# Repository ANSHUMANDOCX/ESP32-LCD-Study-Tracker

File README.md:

# ESP32-LCD-Study-Tracker
Its a Compact Server based study tracker using a OLED display and a ESP32 that help one track their study/work time on particular subjects and also lets use set a target using the interactive web page hosted on the ESP

# Parts used 
- Esp32 Wroom
- 1602 LCD Display
- PCB with onboard programmer

# Why i made this 
This device is made to solve one of the problems i face while studying i keep on getting distracted while i do something and using this device i will be able to keep track of my productive hours so i can get a reality check on long i think i am productive vs how long i actually am !!. 
# Features
- The system uses Display to set timer and keep track of your productive hours. It also has a webpage hosted on the ESP that helps you check on the hours spent at a glance. Also one can set target for the day how much time one needs to be productive for.
- It also has a Log system that logs the time we have spent on something and helps us keep track of how productive one has been. It also has a option to download the log all together as a csv file.
- There is a header for Connecting the LCD using I2C
- There are 3 Buttons for controlling the Display 'Start' , 'Stop' and , 'Change'.
- We can long press the STOP button to turnoff the backlight of the lcd since it could be distracting for some of us.

# Programming
The code is very simple you will need to import the project in platform io and once flash the system image to load the website on the ESP and next upload the main.c file thats it. Also the subject/ Topic one needs to focus on is under a placeholder so anyone can change it according to their needs.  

# PCB and Schematic and CAD

## Build 
https://youtu.be/7US3xBiMZxA?si=RdkPRtCYgrZsQL8k
https://youtu.be/MXmio46lXlo?si=qvKTUyI2eKW5zzEd

# BOM
| Serial No | Product name          | Quantity | Supplier |   Price | Total | Link                                                      |
| --------: | --------------------- | -------: | -------- | ------: | ----: | --------------------------------------------------------- |
|         1 | RC06
03JR-070RL        |      100 | LCSC     | $0.0034 | $0.34 | [LCSC](https://www.lcsc.com/product-detail/C95177.html)   |
|         2 | ME6217C33M5G          |        5 | LCSC     | $0.1219 | $0.61 | [LCSC](https://www.lcsc.com/product-detail/C427602.html)  |
|         3 | CH343P                |        1 | LCSC     | $1.1227 | $1.12 | [LCSC](https://www.lcsc.com/product-detail/C2846043.html) |
|         4 | ESP32-WROOM-32E-N4    |        1 | LCSC     | $3.7668 | $3.77 | [LCSC](https://www.lcsc.com/product-detail/C701341.html)  |
|         5 | TS-1088-AR02016       |       10 | LCSC     | $0.0531 | $0.53 | [LCSC](https://www.lcsc.com/product-detail/C720477.html)  |
|         6 | GT-TC060A-H025-L1S    |        5 | LCSC     | $0.0929 | $0.46 | [LCSC](https://www.lcsc.com/product-detail/C7450623.html) |
|         7 | FRC0603F2201TS        |      100 | LCSC     | $0.0022 | $0.22 | [LCSC](https://www.lcsc.com/product-detail/C2907005.html) |
|         8 | FRC0603F5101TS        |      100 | LCSC     | $0.0021 | $0.21 | [LCSC](https://www.lcsc.com/product-detail/C2907044.html) |
|         9 | RC0603FR-0710KL       |      100 | LCSC     | $0.0040 | $0.40 | [LCSC](https://www.lcsc.com/product-detail/C98220.html)   |
|        10 | CL10B104KB8NNNC       |      200 | LCSC     | $0.0118 | $2.36 | [LCSC](https://www.lcsc.com/product-detail/C1591.html)    |
|        11 | FRC0603F1001TS        |      100 | LCSC     | $0.0029 | $0.29 | [LCSC](https://www.lcsc.com/product-detail/C2907002.html) |
|        12 | SS8050                |       50 | LCSC     | $0.0100 | $0.50 | [LCSC](https://www.lcsc.com/product-detail/C916392.html)  |
|        13 | TYPE-C 16PIN 2MD(073) |       20 | LCSC     | $0.0707 | $1.41 | [LCSC](https://www.lcsc.com/product-detail/C2765186.html) |
|        14 | GRM188R60J476ME15D    |        5 | LCSC     | $0.1934 | $0.97 | [LCSC](https://www.lcsc.com/product-detail/C140782.html)  |
|        15 | CL10A475KP8NNNC       |       50 | LCSC     | $0.0199 | $1.00 | [LCSC](https://www.lcsc.com/product-detail/C1705.html)    |
|        16 | CL10B105KA8NNNC       |       10 | LCSC     | $0.0216 | $0.22 | [LCSC](https://www.lcsc.com/product-detail/C29936.html)   |
|        17 | CL10A106KP8NNNC       |       20 | LCSC     | $0.0353 | $0.71 | [LCSC](https://www.lcsc.com/product-detail/C19702.html)   |
|        18 | PCB       |       1 | JLC     | $2 | $2 | [JLC](jlcpcb.com)   |
|19|LCD Display|1|Robu|$2|$2|[Robu](https://robu.in/product/lcd1602-parallel-lcd-display-with-iic-i2c-interface/)|
||**TOTAL**||||20|||

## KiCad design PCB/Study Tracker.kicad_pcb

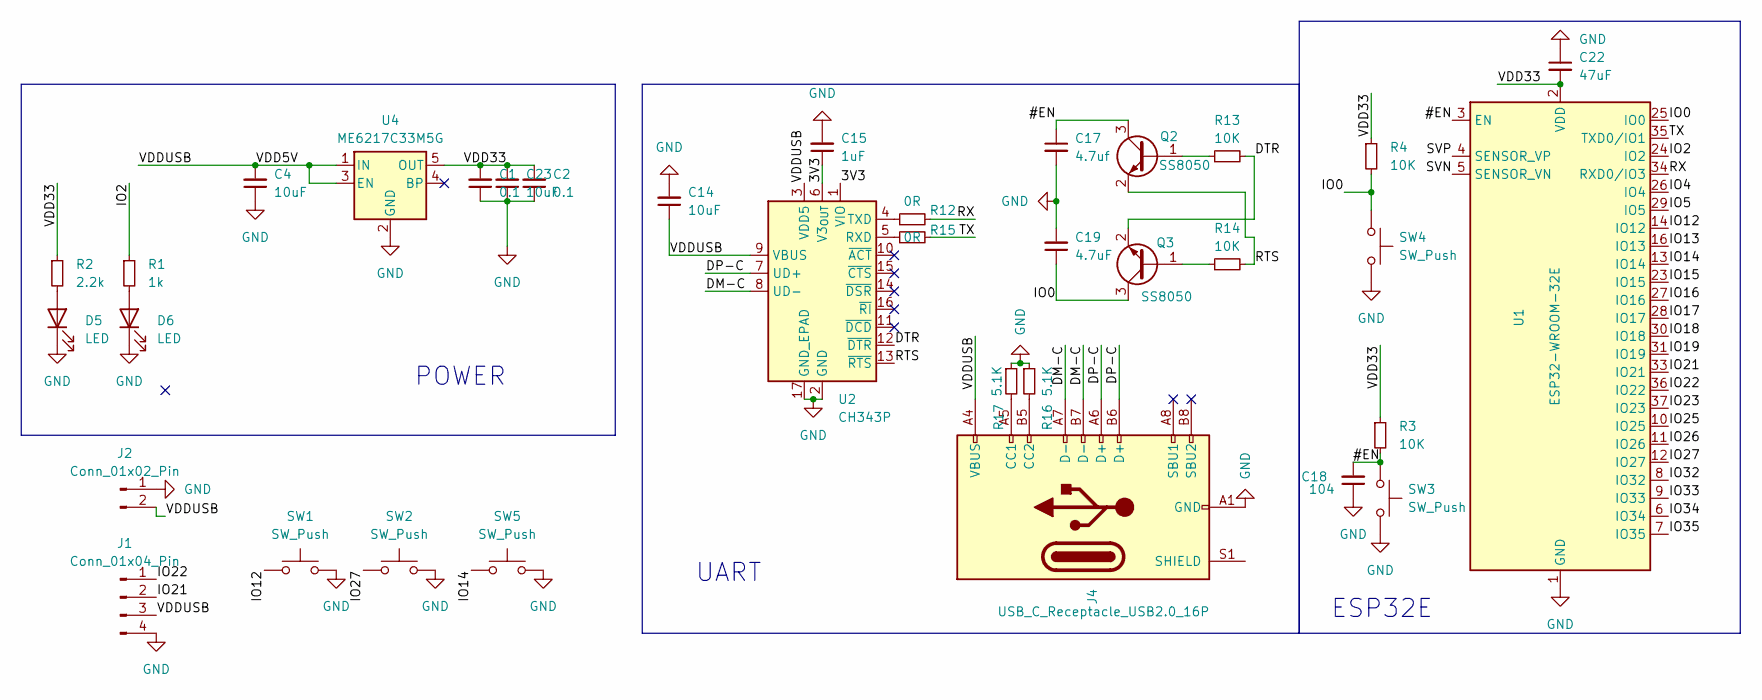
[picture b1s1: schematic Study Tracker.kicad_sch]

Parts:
C1, C2: 0.1; C_0603_1608Metric_Pad1.08x0.95mm_HandSolder
C4, C14, C23: 10uF; C_0603_1608Metric_Pad1.08x0.95mm_HandSolder
C15: 1uF; C_0603_1608Metric_Pad1.08x0.95mm_HandSolder
C17: 4.7uf; C_0603_1608Metric_Pad1.08x0.95mm_HandSolder
C18: 104; C_0603_1608Metric_Pad1.08x0.95mm_HandSolder
C19: 4.7uF; C_0603_1608Metric_Pad1.08x0.95mm_HandSolder
C22: 47uF; C_0603_1608Metric_Pad1.08x0.95mm_HandSolder
D5, D6: LED; LED_0805_2012Metric_Pad1.15x1.40mm_HandSolder
J1: Conn_01x04_Pin; PinHeader_1x04_P2.54mm_Vertical
J2: Conn_01x02_Pin; PinHeader_1x02_P2.54mm_Vertical
J4: USB_C_Receptacle_USB2.0_16P; USB_C_Receptacle_XKB_U262-16XN-4BVC11
Q2, Q3: SS8050; SOT-23
R1: 1k; R_0603_1608Metric_Pad0.98x0.95mm_HandSolder
R2: 2.2k; R_0603_1608Metric_Pad0.98x0.95mm_HandSolder
R3, R4, R13, R14: 10K; R_0603_1608Metric_Pad0.98x0.95mm_HandSolder
R12, R15: 0R; R_0603_1608Metric_Pad0.98x0.95mm_HandSolder
R16, R17: 5.1K; R_0603_1608Metric_Pad0.98x0.95mm_HandSolder
SW1, SW2, SW5: SW_Push; SW_SPST_CK_RS282G05A3
SW3, SW4: SW_Push; SW_Push_SPST_NO_Alps_SKRK
U1: ESP32-WROOM-32E; ESP32-WROOM-32D
U2: CH343P; WCH_QFN-16-1EP_3x3mm_P0.5mm_EP1.8x1.8mm
U4: ME6217C33M5G; SOT-23-5

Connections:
/3V3: C15.1, U2.1 (VIO), U2.6 (V3_{OUT})
/#EN: C17.1, C18.2, Q2.3 (C), R3.2, SW3.1, U1.3 (EN)
/DM-C: J4.A7 (D-), J4.B7 (D-), U2.8 (UD-)
/DP-C: J4.A6 (D+), J4.B6 (D+), U2.7 (UD+)
/DTR: Q3.2 (E), R13.2, U2.12 (~DTR)
/IO0: C19.1, Q3.3 (C), R4.2, SW4.1, U1.25 (IO0)
/IO2: R1.1, U1.24 (IO2)
/IO4: U1.26 (IO4)
/IO5: U1.29 (IO5)
/IO12: SW1.1, U1.14 (IO12)
/IO13: U1.16 (IO13)
/IO14: SW5.1, U1.13 (IO14)
/IO15: U1.23 (IO15); also elsewhere on the board
/IO16: U1.27 (IO16); also elsewhere on the board
/IO17: U1.28 (IO17); also elsewhere on the board
/IO18: U1.30 (IO18); also elsewhere on the board
/IO19: U1.31 (IO19); also elsewhere on the board
/IO21: J1.2, U1.33 (IO21)
/IO22: J1.1, U1.36 (IO22)
/IO23: U1.37 (IO23); also elsewhere on the board
/IO25: U1.10 (IO25)
/IO26: U1.11 (IO26)
/IO27: SW2.1, U1.12 (IO27)
/IO32: U1.8 (IO32)
/IO33: U1.9 (IO33)
/IO34: U1.6 (IO34)
/IO35: U1.7 (IO35)
/RTS: Q2.2 (E), R14.2, U2.13 (~RTS)
/RX: R12.2, U1.34 (RXD0/IO3)
/SVN: U1.5 (SENSOR_VN)
/SVP: U1.4 (SENSOR_VP)
/TX: R15.2, U1.35 (TXD0/IO1)
/VDD5V: C4.2, C14.1, J1.3, J2.2, J4.A4 (VBUS), J4.A9 (VBUS), J4.B4 (VBUS), J4.B9 (VBUS), U2.3 (VDD5), U2.9 (VBUS), U4.1 (IN), U4.3 (EN); also elsewhere on the board
/VDD33: C1.2, C2.2, C22.2, C23.2, R2.1, R3.1, R4.1, U1.2 (VDD), U4.5 (OUT)
GND: C1.1, C2.1, C4.1, C14.2, C15.2, C17.2, C18.1, C19.2, C22.1, C23.1, D5.1 (K), D6.1 (K), J1.4, J2.1, J4.A1 (GND), J4.A12 (GND), J4.B1 (GND), J4.B12 (GND), R16.1, R17.1, SW1.2, SW2.2, SW3.2, SW4.2, SW5.2, U1.1 (GND), U1.15 (GND), U1.38 (GND), U1.39 (GND), U2.2 (GND), U2.17 (GND_EPAD), U4.2 (GND); also elsewhere on the board
unnamed: D5.2 (A), R2.2
unnamed: D6.2 (A), R1.2
unnamed: J4.A5 (CC1), R17.2
unnamed: J4.B5 (CC2), R16.2
unnamed: Q2.1 (B), R13.1
unnamed: Q3.1 (B), R14.1
unnamed: R15.1, U2.5 (RXD)
unnamed: R12.1, U2.4 (TXD)

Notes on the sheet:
UART
POWER
ESP32E

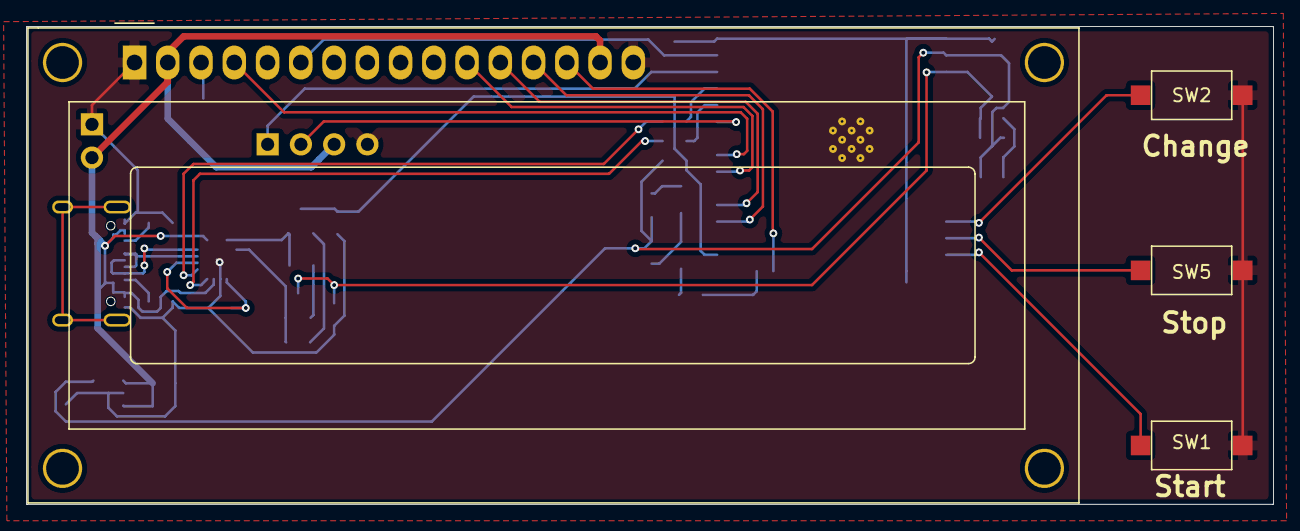
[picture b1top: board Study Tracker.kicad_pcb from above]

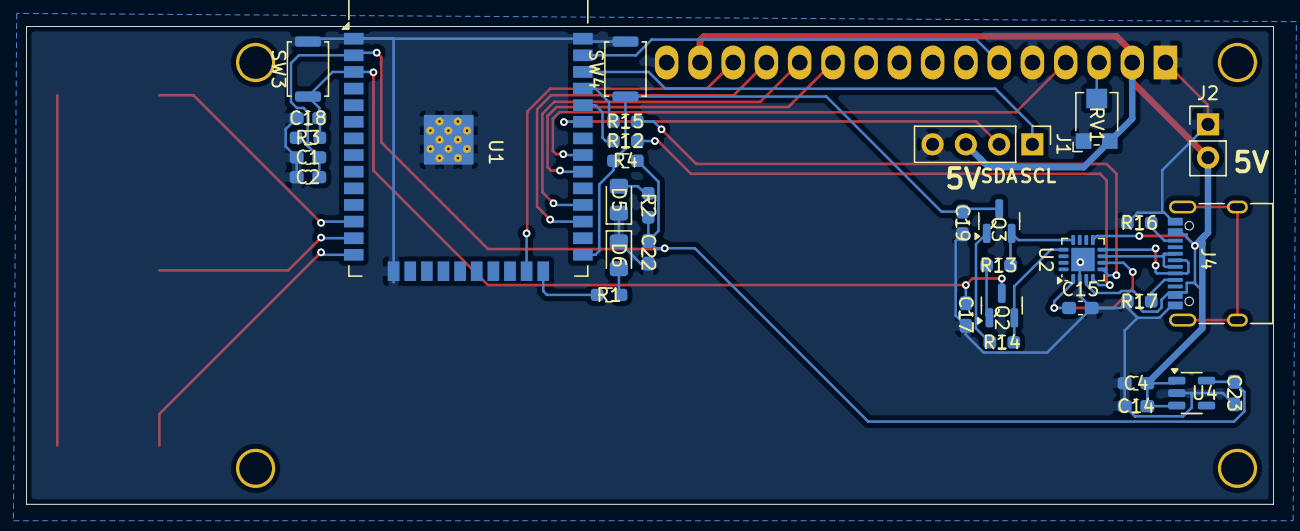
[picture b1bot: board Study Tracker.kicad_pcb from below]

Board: 2 copper layers, 95.2 x 36.5 mm, 37 parts (33 on the bottom side), 33 nets.

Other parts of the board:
DS1: WC1602A
RV1: R_Potentiometer_Small; Potentiometer_Bourns_TC33X_Vertical

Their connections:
/IO15: DS1.14 (D7); also elsewhere on the board
/IO16: DS1.13 (D6); also elsewhere on the board
/IO17: DS1.12 (D5); also elsewhere on the board
/IO18: DS1.11 (D4); also elsewhere on the board
/IO19: DS1.4 (RS); also elsewhere on the board
/IO23: DS1.6 (E); also elsewhere on the board
/VDD5V: DS1.2 (VDD), DS1.15 (LED(+)), RV1.3; also elsewhere on the board
GND: DS1.1 (VSS), DS1.5 (R/W), DS1.16 (LED(-)), RV1.1; also elsewhere on the board
unnamed: DS1.3 (VO), RV1.2
